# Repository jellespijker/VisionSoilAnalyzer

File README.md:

Soil
====

Project for my Bachelor Minor -> Embedded Vision Design and my graduation project -> Mechanical ENgineering @ University of Applied Sciences HAN Arnhem en Nijmegen.

The Doxygen documentation can be found here: http://peer23peer.github.io/VisionSoilAnalyzer/Webpage/index.html
Further documentation indepth background information can be found at the wikie
Youtube movie of the first testrun of the SoilCape can be found here: https://www.youtube.com/watch?v=Ew5GgzQKrGk

The Soil Analyzer is a portable lab that can analyse soil samples and tells the user about it's optical properties. It looks at the texture and describe it as a Particle Size Distribution. This information is presented as a Cumulative Distribution Function (CDF). It also describes the structure of the soil sample and gives information on the sphericity and roundness / angularity. It does so by analysing the contour of particles, describing them as Fourier Descriptors and using a Neural Network to describe it's properties. Finally it gives the color properties in a histogram in the CIE La*b* colorspace, which show correlations with the fertility of the soil. and a histogram of the Redness Index, which gives has a correlation on the iron content.

The analyse is performed on a Beaglebone Black rev C. with the following image Linux arm 3.8.13-bone68 #1 SMP Sat Nov 22 06:51:58 UTC 2014 armv7l armv7l armv7l GNU/Linux

The soil is analyzed using it optical properties. This is done with a 5MP USB webcam with a maximum magnification of 300x. It has a custom cape with which the user can control the device.

Although it uses openCV most Vision algorithms are custom written (part of my Minor demand). openCV is used for camera aquisition and picture storage mostly. This project make use of custom vision, object detection and classification algorithmes.

test

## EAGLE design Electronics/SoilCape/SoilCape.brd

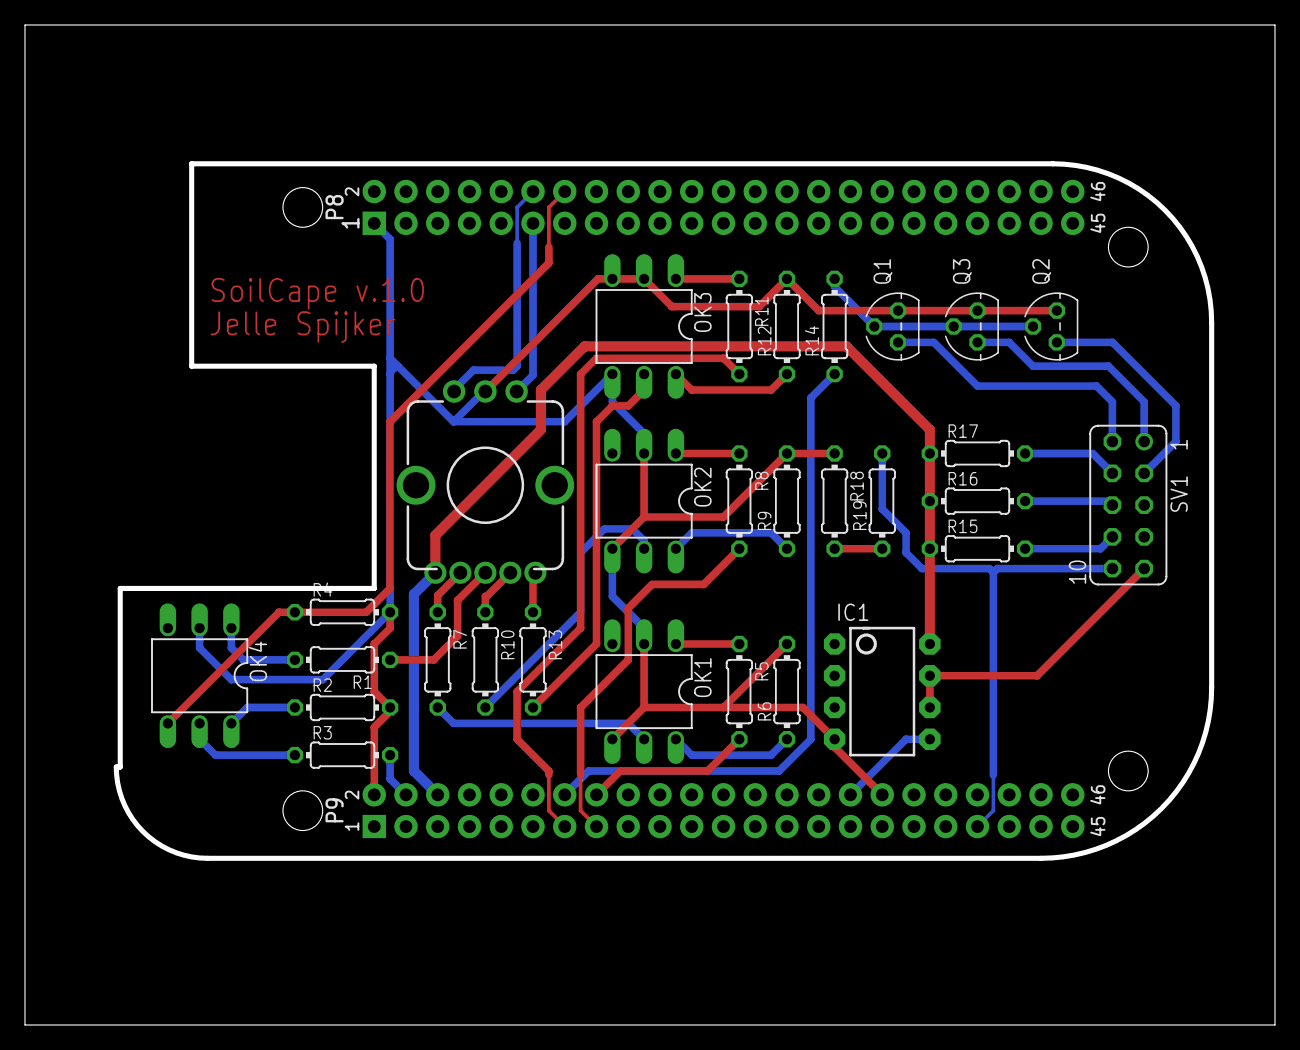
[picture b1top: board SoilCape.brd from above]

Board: 2 copper layers, 99.6 x 79.6 mm, 30 parts (0 on the bottom side), 37 nets.

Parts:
IC1: LM358; DIP08
OK1, OK2, OK3, OK4: 4N25M; DIL06
Q1, Q2, Q3: BC547B; TO92
R1, R2, R3, R4, R5, R6, R7, R8, R9, R10, R11, R12, R13, R14, R15, R16, R17, R18, R19: 0204/7
SV1: FE05-2
SW1: ENCODER_LED_3
U$1: BEAGLE_BONE_BLACK_CAPE

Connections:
ENC_A: SW1.A, U$1.P8.11
ENC_B: SW1.B, U$1.P8.12
GND: IC1.4, OK1.2, OK1.4, OK2.2, OK2.4, OK3.2, OK3.4, OK4.2, Q1.1, Q2.1, Q3.1, R2.2, R4.2, R6.2, R9.2, R12.2, R18.1, SW1.C, U$1.P8.1, U$1.P9.2, U$1.P9.34
GPIO_26: OK4.4, R4.1, U$1.P8.14
GPIO_51: R5.2, U$1.P9.16
unnamed: OK4.5, R3.1
unnamed: OK4.6, R2.1
unnamed: OK1.1, R5.1
unnamed: OK3.1, R11.1
unnamed: OK4.1, R1.2
unnamed: R1.1, SW1.3
unnamed: OK2.1, R8.1
unnamed: OK2.5, R10.2
unnamed: R10.1, SW1.2
unnamed: R13.1, SW1.1
unnamed: OK1.6, R6.1
unnamed: OK3.5, R13.2
unnamed: OK3.6, R12.1
unnamed: R7.1, SW1.4
unnamed: OK1.5, R7.2
unnamed: OK2.6, R9.1
unnamed: IC1.8, R15.1, R16.1, R17.1, SW1.5, U$1.P9.6
unnamed: R8.2, U$1.P9.15
unnamed: R11.2, U$1.P9.13
unnamed: R14.1, U$1.P9.14
unnamed: Q1.2, Q2.2, Q3.2, R14.2
unnamed: Q2.3, SV1.3
unnamed: R15.2, SV1.8
unnamed: Q3.3, SV1.1
unnamed: R16.2, SV1.6
unnamed: R18.2, R19.1
unnamed: IC1.6, IC1.7, SV1.9
unnamed: IC1.5, U$1.P9.32
unnamed: R19.2, SV1.10, U$1.P9.39
unnamed: R17.2, SV1.4
unnamed: Q1.3, SV1.2
VDD_3V3: R3.2, U$1.P9.4

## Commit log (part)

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2015-01-15 :boom::camel: Added .gitattributes & .gitignore files
2015-01-15 startup
    Start of the project
2015-01-15 Test Startup
2015-01-15 Hardware
2015-01-15 Vision Startup
2015-01-15 Test Vision added
2015-01-16 Hardware lib startup
2015-01-16 added README.md
2015-01-16 Matlab functions to proof the concept
    First 10 weeks of the minor
2015-01-16 School documents added
2015-01-16 Hardware Test added
2015-01-18 Filter small blobs when applying the labelled image
2015-01-19 Fixed MatCopy function
2015-01-20 Class MorphologicalFilter added
    Erosion added
2015-01-22 Errosion fixed
2015-01-22 EdgeErode fixed
2015-01-24 SoilCape Testing
2015-01-25 Moved SoilMath types to namespace SoilMath
2015-01-25 removed comment from segment.cpp
2015-01-25 Start of FFT algorithmes
2015-02-04 Currently implementing contour functio
2015-02-08 Contour function completed
2015-02-08 Neural Network Startup
2015-02-11 Genetic Algorithm Startup
2015-02-11 Genetic Algorithm upd.
2015-02-15 Genetic Algorithmes Working
    The syill have to be optimized for the Neural Network
2015-02-21 NN Update
2015-02-24 NN from complex to real
2015-03-08 NN and GA save before major revisement
2015-03-09 Serialization Added to the Neural Network
2015-03-10 SoilAnalyzer Serialization added
2015-03-14 rm old files
2015-03-15 Correction to conversion algorithmes, Statistics and Unit Tests added
2015-03-16 CIE_Lab conversion works
2015-03-17 Welch test added to the statistics class
2015-03-19 Matlab test file added
2015-03-21 copymat works
2015-03-23 Remove duplicated end blob from bloblist
2015-03-24 RemoveBorderBlobs working
2015-03-29 Boost Test Clean up
2015-03-29 Revert "Stats now work for big numbers"
    This reverts commit 030117e7045a0d4ca3ff248128b4c637890e1fec.
2015-03-29 Revert "Revert "Stats now work for big numbers""
    This reverts commit ca201255aab9f4691f8548ce166a45a55dff7640.
2015-03-29 small upd
2015-04-01 Fixed multiple memory leaks in the SoilMath class
2015-04-01 Labelled Blob Memory leak fixed
2015-04-03 Sample and Particle analyze
2015-04-05 Various updates en memory leaks fixed
2015-04-06 morphological work over startingpoint
2015-04-07 Open, Close, Dilate and Erosion working and memchecked
2015-04-07 Soil Sample analyse
    RI en LAB no copy
2015-04-09 SoilPlot StartUp
2015-04-10 SoilPlot Background and label works
2015-04-12 working in progress Line update
2015-04-13 Fix line and copy
2015-04-18 work in progress
2015-04-19 QT build files added
2015-04-19 QT working
2015-04-25 Startup of GUI new file: VSAGUI/VSAGUI.pro new file: VSAGUI/main.cpp new file: VSAGUI/vsagui.cpp new file: VSAGUI/vsagui.h new file: VSAGUI/vsagui.ui
2015-04-25 new file: VSAGUI/Resources/IHClogo.png new file: VSAGUI/Resources/VSA.qrc
2015-04-26 opencv 2 QT functions startup for RGB renamed: src/VisionSoilAnalyzer/VSAGUI/Resources/IHClogo.png -> src/VisionSoilAnalyzer/VSAGUI/IHClogo.png deleted: src/VisionSoilAnalyzer/VSAGUI/Resources/VSA.qr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
2015-04-27 Set right permissions modified: ../../../../.gitignore modified: CMakeLists.txt modified: ComparisionPictures/matlab.mat modified: ComparisionPictures/matlab_blob.mat modified: ComparisionPictures/ma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
2015-04-30 Boost Signals implemented in the Microscope and VSAGUI modified: .gitignore modified: src/VisionSoilAnalyzer/Hardware/Microscope.cpp modified: src/VisionSoilAnalyzer/Hardware/Microscope.h modified: s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
2015-05-01 updated qmake/pro file, Added Save and load for Soil Sample and Neural Net modified: src/VisionSoilAnalyzer/Hardware/Microscope.h modified: src/VisionSoilAnalyzer/Soil/CMakeLists.txt new file: src/Vi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
2015-05-03 Update before switching to Kubuntu new file: .directory new file: src/VisionSoilAnalyzer/.directory new file: src/VisionSoilAnalyzer/Hardware/CMakeLists.txt.user.18 new file: src/VisionSoilAnalyzer/H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
2015-05-06 Hardware settings added modified: src/VisionSoilAnalyzer/.directory modified: src/VisionSoilAnalyzer/Hardware/CMakeLists.txt modified: src/VisionSoilAnalyzer/Hardware/Microscope.cpp modified: src/Vis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
2015-05-20 Start again with the shit
2015-05-22 Stats opdate with mask en zero shift modified: src/VisionSoilAnalyzer/SoilMath/Stats.h src/VisionSoilAnalyzer/VSAGUI_build/ src/VisionSoilAnalyzer/build-SoilMath_Test-Desktop_Qt_5_4_1_GCC_64bit-Debug/
2015-05-24 Soilmath Stats shift bug fixed and mask stat implmented. Furthe testcase added
2015-06-06 Added build directory sturcture
2015-06-06 Create gh-pages branch via GitHub
2015-06-07 nojekyll file added
2015-06-07 SoilCape schematic file added for the wiki
2015-06-07 Doxygen updated GA en FFT
2015-06-08 Various background knowledge documents added about Vision and Neural Networks new file: Documentation/Knowledge/Image Processing/Embedded Vision Design/0_contents.pdf new file: Documentation/Knowledg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
2015-06-20 Comments finnished
2015-06-20 Added a menu item to start Cheese for the microscope
2015-06-21 Import SoilSample Snapshot added Menu item added to import a RGB snapshot which can be analyzed
2015-06-21 Fixed handling of border pixel with kernelsize int enhance
2015-07-13 SoilMath sort with key added
2015-07-14 Linux Script added to install all develpment PPA
2015-07-15 Resources added
2015-07-17 Extract ROI in getBloblist fixed.
2015-07-17 Help wanted with the labelblobs
2015-07-26 Qcustumplot is now a shared lib
2015-07-26 LightCase add
2015-07-27 Sample plate with lid added started working on top
2015-07-28 Vision test functions first stage
2015-07-29 Linux script that sets up the build directory structure. Run this at fresh install and when a new project is created. It doesn't clean up the build structure so if you want to start fresh remove the 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
2015-07-29 Ignore the build directory
2015-07-29 Export to pdf script changed
2015-07-31 Added NEN-ISO-9276
2015-07-31 Connected component labeling works. It is no possible to extract each segemented blob
2015-07-31 Sigsev fault in PrepImg function resolved
2015-08-01 Neural Network Learn UI setup.
2015-08-02 LD_LIBRARY_PATH set to install dir
2015-08-02 Settings update to implement backlight projection and enable/disable HDR
2015-08-02 Started on backlight segmentation
2015-08-04 Test images made with Boris and test functions.
2015-08-05 Microscope class changed big time added Microscope_test routine Keep in mind VSAGUI isn't changed yet.
2015-08-05 Book Foundation of Qt Development added
2015-08-06 Beaglebone and 180x Zoom lens model added
2015-08-06 Setting camera controls is now generic
2015-08-06 Added Cam controls to the settings file
2015-08-07 Added compression to saving/loading of sample file (reduction ~4x file size) lossless compression
    Original VSS file (Sample analysis file) could potential grow to 500mb now it's reduced to 125mb
    It is now necessary to install the 3th party package ZLib
    wget http://zlib.net/zlib-1.2.8.tar.gz
    tar xf zlib-1.2.8.tar.gz
    cd zlib-1.2.8
    ./configure
2015-08-07 QParticleSelector widget created
2015-08-07 VSA main Program created (this will be the new GUI)
2015-08-08 Copyright notice added
2015-08-08 Old Soil lib deleted
2015-08-08 QParticleSelector cleanup
2015-08-08 Serialization added to SoilMath for cv::Mat
2015-08-08 Removed old GUI (VSAGUI) to be replaced with VSA
2015-08-08 Pictureflow QT widget lib used for particle browser
    https://github.com/xiangzhai/pictureflow-qt
2015-08-09 Install bug resolved
2015-08-09 Added CFD function
2015-08-09 Removed floodfil and a few compiler warnings
2015-08-10 Settings file changed
2015-08-11 Settings Dialog Hardware Tab works
2015-08-11 Setting Dialog Vision Settings added
2015-08-12 Enabled use of settings in the GA en NN
2015-08-12 Wrong type for min max weight GA
2015-08-12 Preference tab Works. Printing is still wip
2015-08-12 Save, Load en New Sample implemented.
2015-08-13 ConvertParticle to QImage with white background added
2015-08-13 Commeted out some analysing routines
2015-08-13 Added a white BG function
2015-08-13 Small bug fixes
2015-08-13 Predict switch to support NN study added
2015-08-13 Small pointer bug solved
2015-08-13 PSD Stat Class added
2015-08-14 Calibration function commit
2015-08-14 Added volume display
2015-08-14 Deleting a particle bug fix
2015-08-14 Bug fix finding a cam
2015-08-14 Stat changes
2015-08-14 various
2015-08-15 Settings updated
2015-08-15 Graphs are now updated when a particle is deleted
2015-08-15 No more alpha channel
2015-08-15 Bug fix with loading and copying of the Stats en PSD file
2015-08-15 Shape classification split in roundness and angularity
2015-08-15 Histograms are now updated when classification changes
2015-08-16 Fuck this bug.... Arghhhhhhhhhhhh
2015-08-17 setDisabled function added
2015-08-17 bug fix
2015-08-17 Bug fix with the freeing of the slideImages from memory. (still buggy but not a priority because this leak only occurs when the widget is closed.
2015-08-17 Added some action icons
2015-08-17 Bug fix in de set diasable
2015-08-17 Icons added
2015-08-17 Set the graphs
2015-08-17 Now possible to add the data as std::vector<double> no longer the need to convert from std::vector -> QVector
2015-08-17 Reset zoom on PSD graph with double click
2015-08-17 Two test samples
2015-08-17 Auto progress through the particles when classifing them
2015-08-18 Made the particles float .... like magic
2015-08-18 NeuralNet implemented
2015-08-19 Revolution and bonus system added to GA
2015-08-19 NN test added
2015-08-19 Neuralnet tweaks
2015-08-19 Learn only the angularity
2015-08-19 SIFactor implemented
2015-08-19 Guard against an error that occurs when there are no blobs gathered
2015-08-20 Basic report editor
2015-08-21 Multiple image processing books added
2015-08-21 All the particles are rotated horizontally or vertically
2015-08-21 Set initial roundnes category
2015-08-21 Plot added to to show the Fast Fourier Descriptors for each particle
2015-08-22 FFT bug solved. Don't use a shared FFT object for all particles but a new one for each particle.
2015-08-22 Test results of Gannet20-40 (shift in bins?)
2015-08-22 Fill the FFT graph
2015-08-23 CIE La*b* graph added to the report
2015-08-23 Memory leak fix in the Qreportgenerator
2015-08-23 Memory leak fixed
2015-08-23 No longer a Redness Index Analysis.
2015-08-25 Start work on electronic schematic Version 1.0 Gaara
2015-08-28 Switched to Latex Book form
2015-08-28 Banners added
2015-08-29 Switching to Kernel 4.1.x withe universal capemngr
2015-08-30 Small change
2015-08-30 Documentation added for the AM335x Processor
2015-09-05 Microscope datasheets added
2015-09-13 Datasheet etc update
2015-09-13 Implemented GStreamer to read new camera
2015-09-17 Production files update to account for shrinkage
2015-09-23 First test run of the GUI
2015-09-23 Writing and writing and writing and writing some more
2015-09-27 Legal documentation added
2015-10-05 Text update
2015-10-07 All most there
2015-10-08 Documentation Finished for minor
2015-10-08 As delivered to school
2015-10-25 Thesis assignment added
2015-11-04 Minor Student assignment started
2015-11-04 Minor student assignment description as send to HAN
2015-11-07 typo deconstructor for Stats
2015-11-10 New student proposal
    As send to Sergio and Joost after reviewing with Mario
2015-11-15 Pro file updates
2015-11-15 rename pictureflow pro file
2015-11-15 Build script update
2015-11-15 Auto build for qt 5.2.1
2015-11-18 PDM documentation added
2015-11-21 PDM report update
2015-11-22 Modified PDM report
2015-11-23 Multiple tags added
2015-12-05 fix with PixelFormat switch
2015-12-05 Fix -> selected resolution bug
2015-12-06 Fix zero shake message
2015-12-06 Export Icon added
2015-12-06 Added export struct and translator
2015-12-07 Bug fix #115
2015-12-08 Bug fix #117
2015-12-08 Export images for enhancement #120
2015-12-08 Visual accurate particle shape, bug fix #119
2015-12-08 bug fix #123 cut of particles modified: src/SoilAnalyzer/analyzer.cpp
2015-12-12 Filter button added
2015-12-12 Ignore smaller particles the tend to be artifacts and all current sample doen't go any lower then 0.125
2015-12-12 bug fix#129
2015-12-13 Minor assignment finalized
2015-12-13 PDM stage2 article as submitted to Elburg and Kraandorp

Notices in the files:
parts and their libraries:
SparkFun-AnalogIC: Licensing:Creative Commons ShareAlike 4.0 International - https://creativecommons.org/licenses/by-sa/4.0
